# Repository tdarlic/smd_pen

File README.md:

# smd_pen
Pick and Place Pen Kicad Repository

Videos of development can be found on following links:
(1) https://youtu.be/k6m5PAlaBAs
(2) https://youtu.be/d-iJDVw1978
(3) https://youtu.be/Q16PoXZDJyo
(4) https://youtu.be/s9xIzmQ8K6c

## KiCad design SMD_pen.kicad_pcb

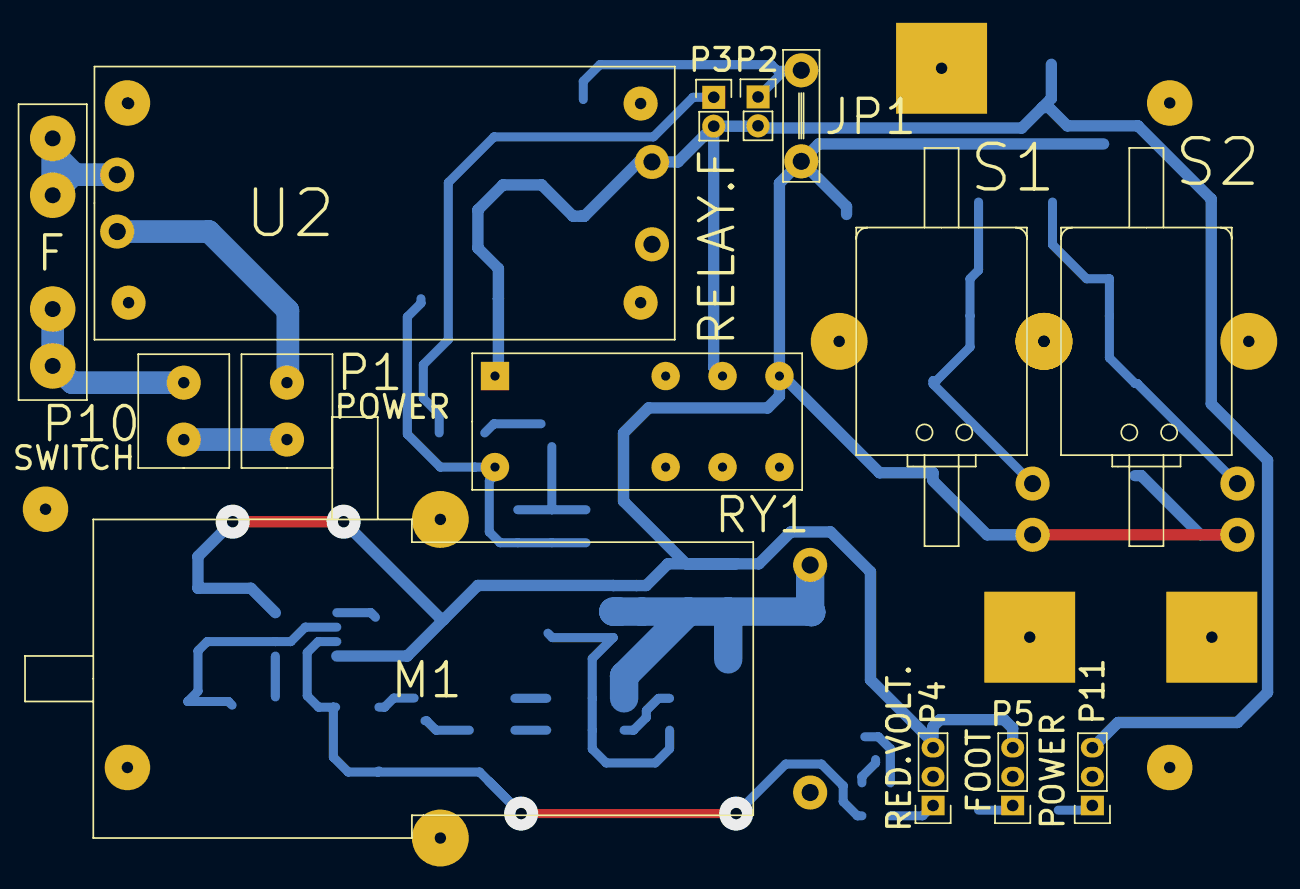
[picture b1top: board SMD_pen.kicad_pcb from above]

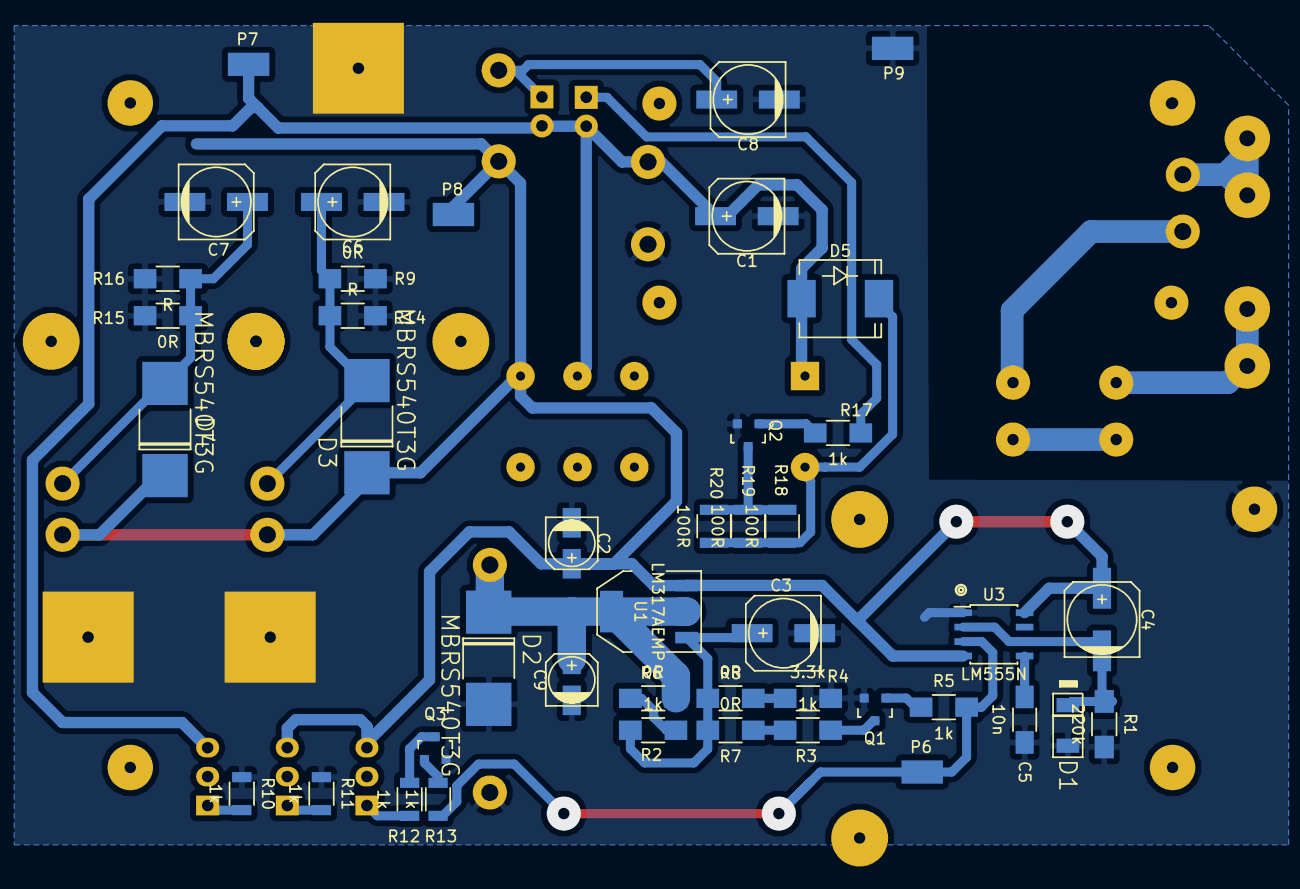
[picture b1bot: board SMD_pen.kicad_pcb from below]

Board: 2 copper layers, 61 parts (43 on the bottom side), 29 nets.

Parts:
C1: 220u; c_elec_6.3x7.7
C2, C9: 1u; c_elec_4x4.5
C3, C8: 10u; c_elec_6.3x7.7
C4: 10U; c_elec_6.3x7.7
C5: 10n; C_1206_HandSoldering
C6, C7: CP; c_elec_6.3x7.7
D1: 1N4148; 1N4148_SMD
D2, D3, D4: MBRS540T3G
D5: SS34; Diode-SMC_Standard
F1: F_Small; FUSE_15_MM_THPCB
H1, H2, H3, H4: HOLE; Mounting_hole_r3
JP1: JUMPER; JUMER_LONG
M1: PUMP; VACUUM_PUMP_6V_EBAY_1
P1: CONN_01X02; TERMBLOCK2_5MM
P2, P3: FOOT_SWITCH; Pin_Header_Straight_1x02
P4: Reduced voltage LED; Pin_Header_Straight_1x03
P5: Foot on LED; Pin_Header_Straight_1x03
P6, P7, P8, P9: TST; S1751-46R
P10: POWER_ON; TERMBLOCK2_5MM
P11: Power on LED; Pin_Header_Straight_1x03
Q1, Q3: BC847; SOT23
Q2: BC817-40; SOT23
R1: 220k; R_1206_HandSoldering
R2, R3, R5, R17: 1k; R_1206_HandSoldering
R4: 3.3k; R_1206_HandSoldering
R6, R7, R8, R9, R15: 0R; R_1206_HandSoldering
R10, R11, R12, R13: 1k; R_1206
R14, R16: R; R_1206_HandSoldering
R18, R19, R20: 100R; R_1210
RY1: Relay_2PDT; SCHRACK_RP310006
S1, S2: SOLENOID; SOLENOID_6V_EBAY_1
U1: LM317AEMP; SOT-223_LM317
U2: Buck_regulator_module_6V; BUCK_REG_6V_EBAY
U3: LM555N; SOIC-8_3.9x4.9mm_Pitch1.27mm

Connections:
555_OUT: P6.1, R5.2, R13.2, U3.3
+6V: C1.1, D5.1, P2.2, P3.2, P7.1, P11.3, RY1.1, RY1.3, U2.3
/TRG_TRESH: C4.2, D1.1, R1.1, U3.2, U3.6
GND: C1.2, C2.2, C3.2, C5.2, C6.2, C7.2, C8.2, C9.2, D1.2, D2.2, M1.2, P9.1, Q1.2, Q2.2, Q3.2, R1.2, R4.1, R9.1, R10.1, R11.1, R14.1, R15.1, R16.1, U2.4, U3.1
unnamed: C3.1, R2.2, R7.2, R8.2, U1.1
unnamed: C5.1, U3.5
unnamed: C6.1, D3.2, R9.2, R14.2, S1.1
unnamed: C7.1, D4.2, R15.2, R16.2, S2.1
unnamed: C8.1, JP1.2, P2.1
unnamed: C9.1, D2.1, M1.1, R6.1, U1.2
unnamed: D5.2, R18.2, R19.2, R20.2, RY1.8
unnamed: F1.1, U2.1
unnamed: F1.2, P10.2
unnamed: P1.1, P10.1
unnamed: P1.2, U2.2
unnamed: P3.1, R17.2
unnamed: P4.1, R12.2
unnamed: P5.1, R11.2
unnamed: P11.1, R10.2
unnamed: Q1.1, R5.1
unnamed: Q1.3, R3.1
unnamed: Q2.1, R17.1
unnamed: Q2.3, R18.1, R19.1, R20.1
unnamed: Q3.1, R13.1
unnamed: Q3.3, R12.1
unnamed: R2.1, R6.2
unnamed: R3.2, R7.1
unnamed: R4.2, R8.1
VCC: C2.1, C4.1, D3.1, D4.1, JP1.1, P4.3, P5.3, P8.1, RY1.4, S1.2, S2.2, U1.3, U3.4, U3.8

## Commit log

2016-07-07 :lollipop: Added .gitattributes & .gitignore files
2016-07-07 Initial commit
    Initial commit
2016-07-07 Crate Readme
